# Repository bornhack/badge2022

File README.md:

# BornHack 2022 Game On Badge

With this badge we are putting the focus on games. With the shape of a small controller and a color LCD screen in the middle it's ready for a bunch of interesting homebrew games.

This badge uses the RP2040 dualcore Cortex M0+ microcontroller from Raspberry Pi and has 16MB of Quad SPI flash for code and probably also a bit of media files.

The badge will come with [CircuitPython](https://circuitpython.org/) preloaded, for a very low barrier of entry, all you need is a USB-C cable, and your favourite texteditor and you are on your way to your own games.

In addition to screen and navigation buttons, there are are also a standard SAO v1.96bis connector and a Qwiic/Stemma QT connector for interfacing with modules in those eco-systems over I2C.

For those that want to experiment with expanding the badge with a bit more hardware, there is a prototyping area on the left side, maybe for a custom joystick, a preasure sensitive e-textile sensor or something else that works with your game. To interface with the RP2040, there are a few I/O hookup points along the exdge, that support either crocodile test leads, conductive thread or regular wire soldered down, depending on what you are making. Two of those I/O's have analog input capabilities, and there are two more analog inputs in the GPIO1 and GPIO2 pins of the SAO connector, if you need more.

There are also some mounting holes (they fit M3 screws), for mounting an additional add-on board or maybe a 3D printed case. If you want to make your own expansion board, there is [an add-on template](https://github.com/bornhack/badge2022/tree/add-on-template) (it's in the `add-on-template` branch in this repo), that you can open up and customize to your liking before ordering. There will also be some prototyping boards available in the Hardware Hacking Tent at BornHack along with some basic parts, similar to last year.

## CircuitPython restore file

If you flash the board with something else and want to get back to CircuitPython, you can bring the badge into the UF2 bootloader by holding the BOOT button and pressing RESET (you can also hold BOOT when powering on). The badge will then show up as a mass storage device called something like RP2-? which is the build in bootloader and you simply copy over the [firmware.uf2](https://github.com/bornhack/badge2022/raw/hardware/firmware.uf2) file from the root of this repository. The badge will reboot, and you are then back to CircuitPython

The original python files that was on the badge when handed out are in the [cp-init branch](https://github.com/bornhack/badge2022/tree/cp-init)

## Designed in KiCad v6

This board is designed in KiCad v6. To open the project, you will need to install a recent release version or one of the nightly builds, KiCad v5 won't open this design. The [schematic as a PDF](https://github.com/bornhack/badge2022/raw/hardware/schematic.pdf) is included for reference.

## Projects running on the badge

Feel free to submit a PR adding on to this list with your project that runs on the badge.

- [Video player and AM radio transmitter](https://github.com/kbeckmann/bornhack-badge2022-audiovideo) by Konrad Beckmann. See it in action [here](https://twitter.com/kbeckmann/status/1556251282742075393) and [here](https://twitter.com/kbeckmann/status/1555895391463346176).
- [Small adventure hack'n'slash game](https://github.com/MrJavaWolf/BornHack2022Game) by Jens 'JWolf' Larsen. See the [preview here](https://raw.githubusercontent.com/MrJavaWolf/BornHack2022Game/main/resources/teaser-video.mp4).
- [Flappybirds](https://github.com/pietervdvn/BadgeMap/tree/feature/calendar/bornhack) by Pieter Vander Vennet.
- [Pacman](https://github.com/glymphie/bh2022-pacman-game) by Glymphie.

## License

The contents of this repository is released under the following license:

* the "Creative Commons Attribution-ShareAlike 4.0 International License"
  (CC BY-SA 4.0) full text of this license is included in the LICENSE file
  and a copy can also be found at
  [http://creativecommons.org/licenses/by-sa/4.0/](http://creativecommons.org/licenses/by-sa/4.0/)

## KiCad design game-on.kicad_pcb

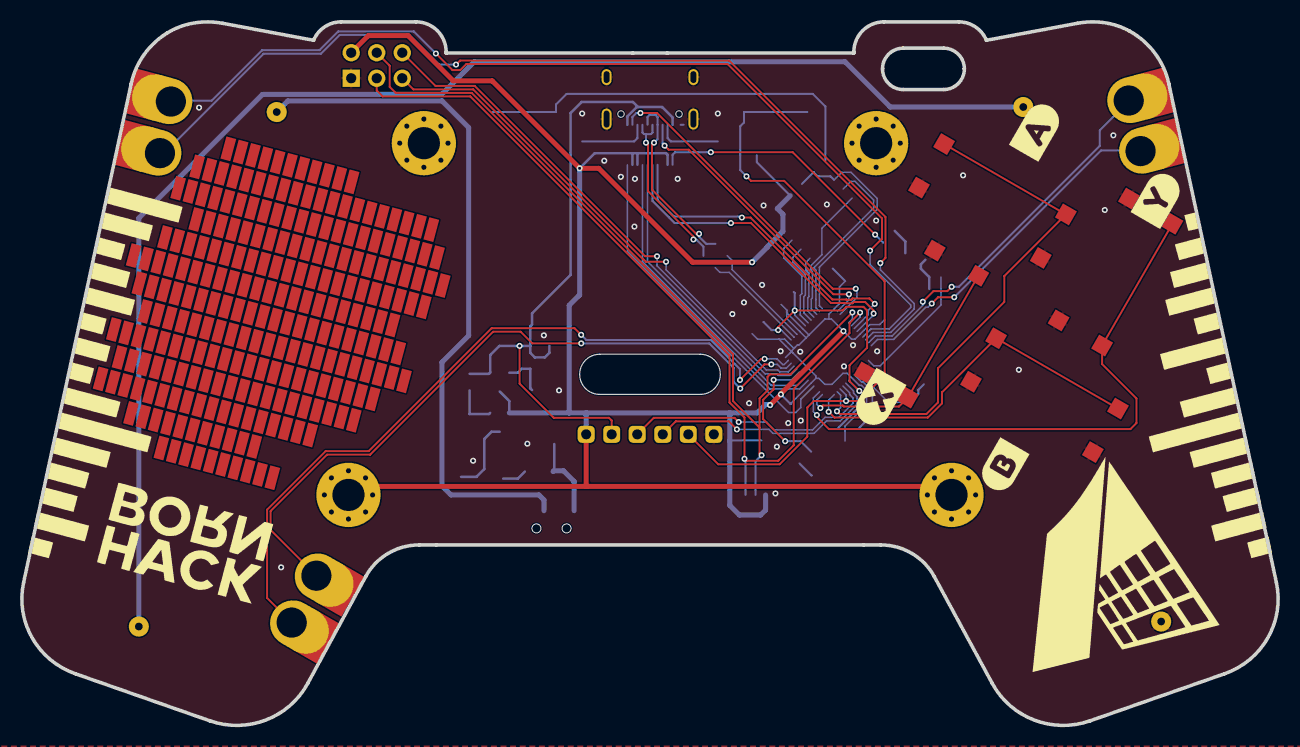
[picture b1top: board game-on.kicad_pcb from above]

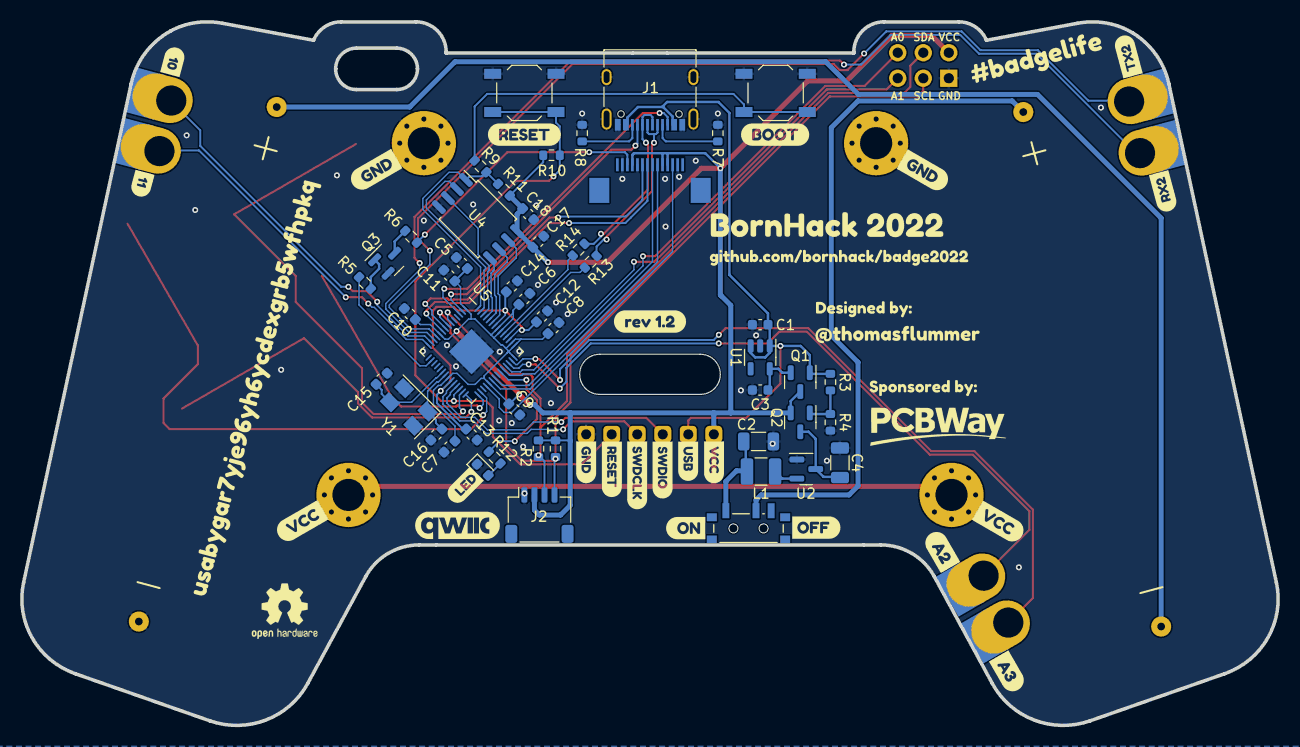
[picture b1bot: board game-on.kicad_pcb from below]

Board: 2 copper layers, 125.0 x 70.0 mm, 95 parts (78 on the bottom side), 56 nets.

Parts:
BT1, BT2: Battery_Cell; Single_AA
C1, C3: 1uF; C_0603_1608Metric
C2, C4: 100uF; C_1206_3216Metric
C5, C12, C17: 2.2uF; C_0603_1608Metric
C6, C7, C8, C9, C10, C11, C13, C14, C18: 100nF; C_0603_1608Metric
C15, C16: 30pF; C_0603_1608Metric
D1: LED; LED_0603_1608Metric
J1: USB_C; USB_C_Receptacle_XKB_U262-16XN-4BVC11
J2: Qwiic; JST_SH_SM04B-SRSS-TB_1x04-1MP_P1.00mm_Horizontal
J3: DEBUG; PinHeader_1x06_P2.54mm_Vertical
L1: 47uH; L_1210_3225Metric
Q1: CJ2302; SOT-23
Q2: CJ2305; SOT-23
Q3: BC817; SOT-23
R1, R2, R10, R11: 10k; R_0603_1608Metric
R3: 4.7k; R_0603_1608Metric
R4: 6.8k; R_0603_1608Metric
R5: 1K; R_0603_1608Metric
R6, R13, R14: 27R; R_0603_1608Metric
R7, R8: 5.1k; R_0603_1608Metric
R9, R12: 1k; R_0603_1608Metric
SW1: POWER; SW_SPDT_PCM12
SW2: A; 12x12x7.3mm_Tactile_Switch
SW3: B; 12x12x7.3mm_Tactile_Switch
SW4: X; 12x12x7.3mm_Tactile_Switch
SW5: Y; 12x12x7.3mm_Tactile_Switch
SW6: RESET; SW_SPST_TL3342
SW7: BOOT; SW_SPST_TL3342
TP1: GPIO8; PTH_Edge_Proto_Connector
TP2: GPIO9; PTH_Edge_Proto_Connector
TP3: GPIO11; PTH_Edge_Proto_Connector
TP4: GPIO10; PTH_Edge_Proto_Connector
TP5: GPIO28; PTH_Edge_Proto_Connector
TP6: GPIO29; PTH_Edge_Proto_Connector
U1: HX9193-33GB; SOT-23-5
U2: QX2304; SOT-23
U3: ST7735S-SPI-14pin; 1.77inch_128x160_ST7735S_SPI
U4: W25QXX128MBIT; SOIC-8_5.23x5.23mm_P1.27mm
U5: RP2040; QFN-56_EP_7x7_Pitch0.4mm
X1: #badgelife; Badgelife-SAOv169-BADGE-2x3
Y1: 12MHz; Crystal_SMD_5032-4Pin_5.0x3.2mm
kibuzzard-62AC43D4: G***; kibuzzard-62AC43D4
kibuzzard-62AC43F5: G***; kibuzzard-62AC43F5
kibuzzard-62AC44E7: G***; kibuzzard-62AC44E7
kibuzzard-62AC441C: G***; kibuzzard-62AC441C
kibuzzard-62AC5196: G***; kibuzzard-62AC5196
kibuzzard-629F9B54: G***; kibuzzard-629F9B54
kibuzzard-629F9BBE: G***; kibuzzard-629F9BBE
kibuzzard-629F9DE1: G***; kibuzzard-629F9DE1
kibuzzard-629F9DF6: G***; kibuzzard-629F9DF6
kibuzzard-629F9E6D: G***; kibuzzard-629F9E6D
kibuzzard-629F9E81: G***; kibuzzard-629F9E81
kibuzzard-629F97EB: G***; kibuzzard-629F97EB
kibuzzard-629F98B0: G***; kibuzzard-629F98B0
kibuzzard-629F98F3: G***; kibuzzard-629F98F3
kibuzzard-629F99C8: G***; kibuzzard-629F99C8
kibuzzard-629F99E6: G***; kibuzzard-629F99E6
kibuzzard-629F9808: G***; kibuzzard-629F9808
kibuzzard-629F9825: G***; kibuzzard-629F9825
kibuzzard-629F9902: G***; kibuzzard-629F9902
kibuzzard-629FA1A3: G***; kibuzzard-629FA1A3
kibuzzard-629FA2B0: G***; kibuzzard-629FA2B0
kibuzzard-629FA2CB: G***; kibuzzard-629FA2CB
kibuzzard-629FA2E9: G***; kibuzzard-629FA2E9
kibuzzard-629FA297: G***; kibuzzard-629FA297
kibuzzard-629FA844: G***; kibuzzard-629FA844
kibuzzard-629FB3A9: G***; kibuzzard-629FB3A9
kibuzzard-629FB4BE: G***; kibuzzard-629FB4BE
kibuzzard-629FB33D: G***; kibuzzard-629FB33D
kibuzzard-629FB35D: G***; kibuzzard-629FB35D
kibuzzard-629FB38F: G***; kibuzzard-629FB38F
kibuzzard-629FB41C: G***; kibuzzard-629FB41C
kibuzzard-629FB440: G***; kibuzzard-629FB440
kibuzzard-629FB487: G***; kibuzzard-629FB487

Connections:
+1V1: C12.1, C13.1, C14.1, U5.23 (DVDD), U5.45 (VREG_VOUT), U5.50 (DVDD)
/A0: U5.38 (GPIO26), X1.5 (GPIO1)
/A1: U5.39 (GPIO27), X1.6 (GPIO2)
/Buttons/A: SW2.1 (A), U5.27 (GPIO16)
/Buttons/B: SW3.1 (A), U5.28 (GPIO17)
/Buttons/X: SW4.1 (A), U5.29 (GPIO18)
/Buttons/Y: SW5.1 (A), U5.30 (GPIO19)
/Display/BACKLIGHT: R5.2, U5.16 (GPIO13)
/Display/COPI: U3.8 (SDA), U5.35 (GPIO23)
/Display/CS: U3.12 (CS), U5.32 (GPIO21)
/Display/D/C: U3.7 (A0), U5.9 (GPIO7)
/Display/RESET: U3.6 (RES), U5.8 (GPIO6)
/Display/SCK: U3.9 (SCK), U5.34 (GPIO22)
/PSU 2xAA/BAT+: BT1.1 (+), SW1.2 (B)
/PSU 2xAA/BOOST_OUT: C4.1, Q2.3 (D), U2.3 (VOUT)
/PSU 2xAA/VREG_OUT: C3.1, Q1.2 (S), U1.5 (VOUT)
/RP2040/A2: TP5.1, U5.40 (GPIO28)
/RP2040/A3: TP6.1, U5.41 (GPIO29)
/RP2040/D+: R14.2, U5.47 (USB_D+)
/RP2040/D-: R13.2, U5.46 (USB_D-)
/RP2040/I2C_~INT/TX2: TP1.1, U5.11 (GPIO8)
/RP2040/QSPI-0: U4.5 (DI(IO0)), U5.53 (QSPI_SD0)
/RP2040/QSPI-1: U4.2 (DO(IO1)), U5.55 (QSPI_SD1)
/RP2040/QSPI-2: U4.3 (IO2), U5.54 (QSPI_SD2)
/RP2040/QSPI-3: U4.7 (IO3), U5.51 (QSPI_SD3)
/RP2040/QSPI-CLK: U4.6 (CLK), U5.52 (QSPI_SCLK)
/RP2040/QSPI-~CS: R9.2, R11.2, U4.1 (~CS), U5.56 (~QSPI_CS)
/RP2040/SBU1: J1.A8 (SBU1), U5.2 (GPIO0)
/RP2040/SBU2: J1.B8 (SBU2), U5.3 (GPIO1)
/RP2040/SDIO_DAT1/AUD_IN: TP3.1, U5.14 (GPIO11)
/RP2040/SDIO_DAT2/AUD_OUT: TP4.1, U5.13 (GPIO10)
/RP2040/SPI_~CS1/SDIO_DAT3/RX2: TP2.1, U5.12 (GPIO9)
/RP2040/SWDCLK: J3.4, U5.24 (SWCLK)
/RP2040/SWDIO: J3.3, U5.25 (SWDIO)
/RP2040/USB_D+: J1.A6 (D+), J1.B6 (D+), R14.1
/RP2040/USB_D-: J1.A7 (D-), J1.B7 (D-), R13.1
/RP2040/USB_VBUS: C1.1, J1.A4 (VBUS), J1.A9 (VBUS), J1.B4 (VBUS), J1.B9 (VBUS), J3.2, Q1.1 (G), R3.1, U1.1 (VIN), U1.3 (EN)
/RP2040/~BOOT: R9.1, SW7.2 (B)
/RP2040/~RESET: J3.5, R10.2, SW6.2 (B), U5.26 (RUN)
/SCL: J2.4, R1.2, U5.7 (GPIO5), X1.4 (SCL)
/SDA: J2.3, R2.2, U5.6 (GPIO4), X1.3 (SDA)
GND: BT2.2 (-), C1.2, C2.2, C3.2, C4.2, C5.2, C6.2, C7.2, C8.2, C9.2, C10.2, C11.2, C12.2, C13.2, C14.2, C15.1, C16.1, C17.2, C18.2, D1.1 (K), J1.A1 (GND), J1.A12 (GND), J1.B1 (GND), J1.B12 (GND), J1.S1 (SHIELD), J2.1, J3.6, Q3.2 (E), R4.2, R7.1, R8.1, SW2.2 (B), SW3.2 (B), SW4.2 (B), SW5.2 (B), SW6.1 (A), SW7.1 (A), U1.2 (GND), U2.1 (GND), U3.2 (GND), U3.5 (GND), U3.13 (GND), U4.4 (GND), U5.19 (TESTEN), U5.57 (GND), X1.2 (GND), Y1.2, Y1.4
unnamed: BT1.2 (-), BT2.1 (+)
unnamed: C2.1, L1.1, SW1.1 (A)
unnamed: C15.2, U5.20 (XIN), Y1.3
unnamed: C16.2, U5.21 (XOUT), Y1.1
unnamed: D1.2 (A), R12.1
unnamed: J1.A5 (CC1), R7.2
unnamed: J1.B5 (CC2), R8.2
unnamed: L1.2, U2.2 (LX)
unnamed: Q2.1 (G), R3.2, R4.1
unnamed: Q3.1 (B), R5.1
unnamed: Q3.3 (C), R6.2
unnamed: R6.1, U3.3 (LED-)
unnamed: R12.2, U5.37 (GPIO25)
VCC: C5.1, C6.1, C7.1, C8.1, C9.1, C10.1, C11.1, C17.1, C18.1, J2.2, J3.1, Q1.3 (D), Q2.2 (S), R1.1, R2.1, R10.1, R11.1, U3.4 (LED+), U3.10 (VCC), U3.11 (IOVCC), U4.8 (VCC), U5.1 (IOVDD), U5.10 (IOVDD), U5.22 (IOVDD), U5.33 (IOVDD), U5.42 (IOVDD), U5.43 (ADC_AVDD), U5.44 (VREG_VIN), U5.48 (USB_VDD), U5.49 (IOVDD), X1.1 (VCC)

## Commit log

2022-06-12 Tweaked a few values
2022-06-12 Added interactive HTML BOM
2022-06-12 Added PDF schematic
2022-06-17 Adjusted fine pitch pads to allow matte black soldermask between
    Also added a bit of silkscreen tweaks
2022-06-26 Inition version of the add-on template
2022-06-26 Added license file
2022-07-05 Added readme and photo
2022-07-06 Added readme and gerbers in addition to adding stonsor logo in silkscreen
2022-07-06 Saved export settings
2022-07-11 Fixed issue with logo graphics breaking up
2022-08-01 Initial CircuitPython screen test
2022-08-02 Write code and make apps folder
2022-08-02 Change delay
2022-08-06 Initial commit
    CircuitPython files initially on the badge at handout time
2022-08-06 Added firmware restore information
2022-08-07 readme: Add a section with community projects running on the badge.
2022-08-08 readme: Add a section with community projects running on the badge. (#2)
2022-08-08 Update README.md
    Added: Reference to my small adventure hack'n'slash game
2022-08-08 Update README.md (#3)
    Added: Reference to my small adventure hack'n'slash game
2022-08-08 Added link to Pieters flappybird for the badge
2022-08-10 Added Pacman to Projects running on the badge
2022-08-11 Added Pacman to Projects running on the badge (#4)
2022-08-20 Fix memory leak
    Create a new displayio.Group on each draw rather than reusing one in
    global scope thereby leaking memory fast.
